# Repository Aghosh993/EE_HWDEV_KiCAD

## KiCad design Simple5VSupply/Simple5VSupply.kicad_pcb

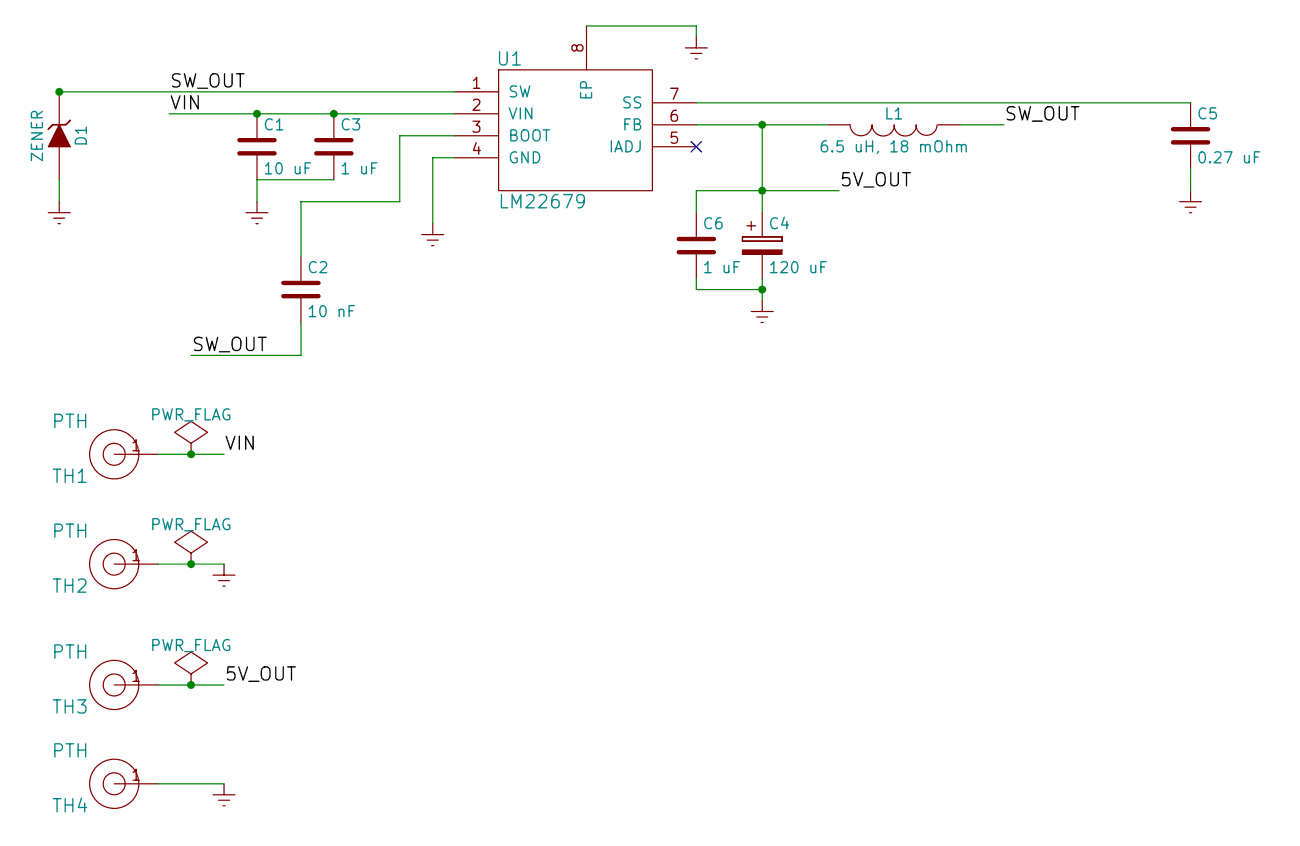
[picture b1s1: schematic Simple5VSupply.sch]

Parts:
C1: 10 uF; C_1210_HandSoldering
C2: 10 nF; C_0805_HandSoldering
C3, C6: 1 uF; C_0603_HandSoldering
C4: 120 uF; Radial_SMD_8mm
C5: 0.27 uF; C_0805_HandSoldering
D1: ZENER; DPAK_TO252AA_CUSTOM
L1: 6.5 uH, 18 mOhm; SRR1208
TH1, TH2, TH3, TH4: PTH
U1: LM22679; TI_TO-263

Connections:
/5V_OUT: C4.1, C6.1, L1.2, TH3.1, U1.6 (FB)
/SW_OUT: C2.2, D1.1 (K), L1.1, U1.1 (SW)
/VIN: C1.1, C3.1, TH1.1, U1.2 (VIN)
Earth: C1.2, C3.2, C4.2, C5.2, C6.2, D1.2 (A), TH2.1, TH4.1, U1.4 (GND), U1.8 (EP)
unnamed: C2.1, U1.3 (BOOT)
unnamed: C5.1, U1.7 (SS)

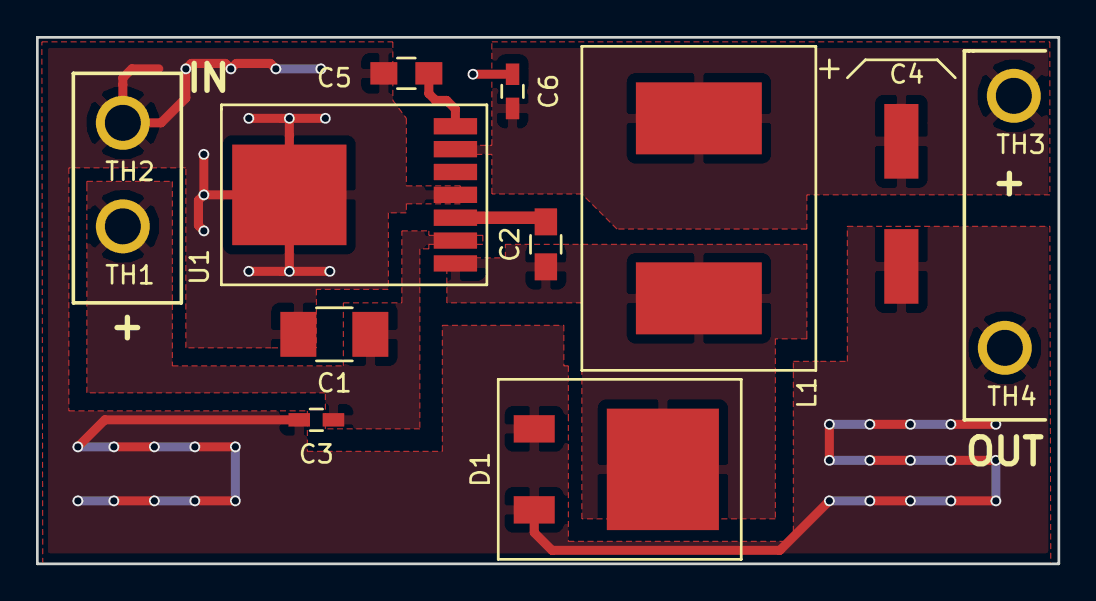
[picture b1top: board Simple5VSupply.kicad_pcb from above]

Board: 2 copper layers, 56.8 x 29.2 mm, 13 parts (0 on the bottom side), 6 nets.

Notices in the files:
Simple5VSupply/Simple5VSupply.kicad_pcb:
(c) 2016
